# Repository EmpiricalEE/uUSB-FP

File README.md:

# Joulescope JS220 uUSB Front Panel

> ⚠️ This is a **read-only** mirror of a private SVN repository. See the [Product Page](https://www.tindie.com/products/empirical-ee/uusb-front-panel/) on Tindie.

The uUSB FP is a versatile panel for the [Joulescope JS220](https://www.joulescope.com/products/js220-joulescope-precision-energy-analyzer) power analyser that enables power measurement of any USB device.

## Key Features

- Multiple USB connector types supported:
    - USB Type-C
    - USB Type-A
    - Micro USB
    - Screw terminals for custom connections
- Supports any combination of input terminal and output terminal
- Compatible with Joulescope JS220
- Supports USB 2.0 High Speed (HS) data pass-through with minor performance impact

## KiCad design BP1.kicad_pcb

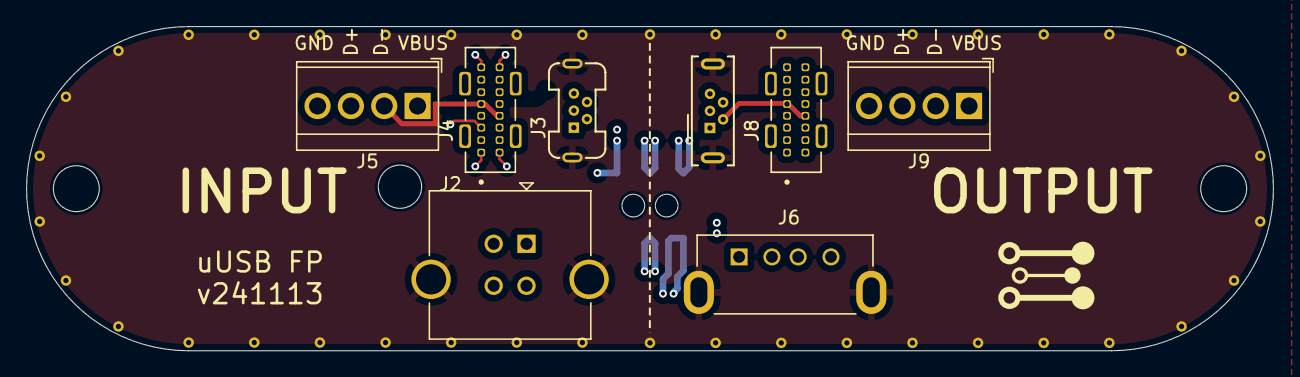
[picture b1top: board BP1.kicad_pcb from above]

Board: 4 copper layers, 95.0 x 24.7 mm, 10 parts (0 on the bottom side), 8 nets.

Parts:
G1: Logo_Empirical; logo_empirical_7x5mm
J1: JS220
J2: USB_B_In; USB_B_CUI_Devices_UJ2-BV-1-TH_Vertical
J3: USB_B_Micro_In; USB_Micro-B_GCT_USB3145-30-1-A_Vertical
J4: USB_C_In; CUI_UJ20-C-V-C-3-SMT-TR
J5: Screw_In; TerminalBlock_Wuerth_691210910004-2.54-4P_1x04_P2.54mm_Hori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
J6: USB_A_Out; USB_A_Adam_Tech_USB-A-S-VT_Vertical
J7: USB_AB_Micro_Out; USB_Micro-AB_GCT_USB3106-30-0230-A_Vertical
J8: USB_C_Out; CUI_UJ20-C-V-C-3-SMT-TR
J9: Screw_Out; TerminalBlock_Wuerth_691210910004-2.54-4P_1x04_P2.54mm_Hori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

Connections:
/D+: J2.3 (D+), J3.3 (D+), J4.A6 (D+), J4.B6 (D+), J5.3, J6.3 (D+), J7.3 (D+), J8.A6 (D+), J8.B6 (D+), J9.3
/D-: J2.2 (D-), J3.2 (D-), J4.A7 (D-), J4.B7 (D-), J5.2, J6.2 (D-), J7.2 (D-), J8.A7 (D-), J8.B7 (D-), J9.2
Earth: J1.7 (SHIELD), J2.5 (Shield), J3.6 (Shield), J6.5 (Shield), J7.6 (Shield)
GND: J1.5 (V-), J2.4 (GND), J3.5 (GND), J4.A1 (GND), J4.A12 (GND), J4.B1 (GND), J4.B12 (GND), J5.4, J6.4 (GND), J7.5 (GND), J8.A1 (GND), J8.A12 (GND), J8.B1 (GND), J8.B12 (GND), J9.4
unnamed: J4.A5 (CC1), J8.A5 (CC1)
unnamed: J4.B5 (CC2), J8.B5 (CC2)
VCC: J1.1 (I+), J1.2 (I+), J1.6 (V+), J2.1 (VBUS), J3.1 (VBUS), J4.A4 (VBUS), J4.A9 (VBUS), J4.B4 (VBUS), J4.B9 (VBUS), J5.1
VDD: J1.3 (I-), J1.4 (I-), J6.1 (VBUS), J7.1 (VBUS), J8.A4 (VBUS), J8.A9 (VBUS), J8.B4 (VBUS), J8.B9 (VBUS), J9.1

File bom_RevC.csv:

Reference,Value,Datasheet,Footprint,Qty,DNP,Description,MPN,Manufacturer,Order Code,Supplier,Critical
J1,JS220,https://mm.digikey.com/Volume0/opasdata/d220001/medias/docus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,Joulescope:JS220,1,,Joulescope 220 front panel outline and connector,TSM-103-01-S-DV-A,Samtec Inc.,TSM-103-01-S-DV-A-ND,Digi-Key,
J2,USB_B_In,https://www.cuidevices.com/product/resource/uj2-bv-1-th.pdf,Becquerel:USB_B_CUI_Devices_UJ2-BV-1-TH_Vertical,1,,USB Type B connector,UJ2-BV-1-TH,CUI Devices,102-4000-ND,Digi-Key,
J3,USB_B_Micro_In,https://gct.co/files/specs/usb3145-spec.pdf,Becquerel:USB_Micro-B_GCT_USB3145-30-1-A_Vertical,1,,USB Micro Type B connector,USB3145-30-1-A,GCT,2073-USB3145-30-1-ACT-ND,Digi-Key,
J4,USB_C_In,https://mm.digikey.com/Volume0/opasdata/d220001/medias/docus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,Becquerel:USB_C_Receptacle_GCT_USB4115-03-C,1,,USB 2.0-only 24P Type-C Receptacle connector,UJ20-C-V-C-3-SMT-TR,Same Sky,2223-UJ20-C-V-C-3-SMT-TR-ND,Digi-Key,
J5,Screw_In,https://www.we-online.com/katalog/datasheet/6912109100xx.pdf,Becquerel:TerminalBlock_Wuerth_691210910004-2.54-4P_1x04_P2.54mm_Horizontal,1,,"Generic screw terminal, single row, 01x04, script generated (kicad-library-utils/schlib/autogen/connector/)",691210910004,Würth Elektronik,732-691210910004-ND,Digi-Key,
J6,USB_A_Out,https://app.adam-tech.com/products/download/data_sheet/19586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,Becquerel:USB_A_Adam_Tech_USB-A-S-VT_Vertical,1,,USB Type A connector,USB-A-S-VT,Adam Tech,2057-USB-A-S-VT-ND,Digi-Key,
J7,USB_AB_Micro_Out,https://gct.co/files/specs/usb3106-spec.pdf,Becquerel:USB_Micro-AB_GCT_USB3106-30-0230-A_Vertical,1,,USB Micro Type B connector,USB3106-30-0230-A,GCT,2073-USB3106-30-0230-ACT-ND,Digi-Key,
J8,USB_C_Out,https://mm.digikey.com/Volume0/opasdata/d220001/medias/docus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,Becquerel:USB_C_Receptacle_GCT_USB4115-03-C,1,,USB 2.0-only 24P Type-C Receptacle connector,UJ20-C-V-C-3-SMT-TR,Same Sky,2223-UJ20-C-V-C-3-SMT-TR-ND,Digi-Key,
J9,Screw_Out,https://www.we-online.com/katalog/datasheet/6912109100xx.pdf,Becquerel:TerminalBlock_Wuerth_691210910004-2.54-4P_1x04_P2.54mm_Horizontal,1,,"Generic screw terminal, single row, 01x04, script generated (kicad-library-utils/schlib/autogen/connector/)",691210910004,Würth Elektronik,732-691210910004-ND,Digi-Key,

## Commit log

2024-12-10 Rename bom_RevC.csv to output/bom_RevC.csv
2024-12-10 Rename BP1_3D_v240915.jpg to output/BP1_3D_v240915.jpg
2024-12-10 Rename BP1_SCH_RevC.pdf to output/BP1_SCH_RevC.pdf
2024-12-10 Rename BP1_Gerbers_v241112.zip to output/BP1_Gerbers_v241112.zip
2024-12-10 Rename README.md to output/README.md
2024-12-10 Add Tindie URL to README.md
